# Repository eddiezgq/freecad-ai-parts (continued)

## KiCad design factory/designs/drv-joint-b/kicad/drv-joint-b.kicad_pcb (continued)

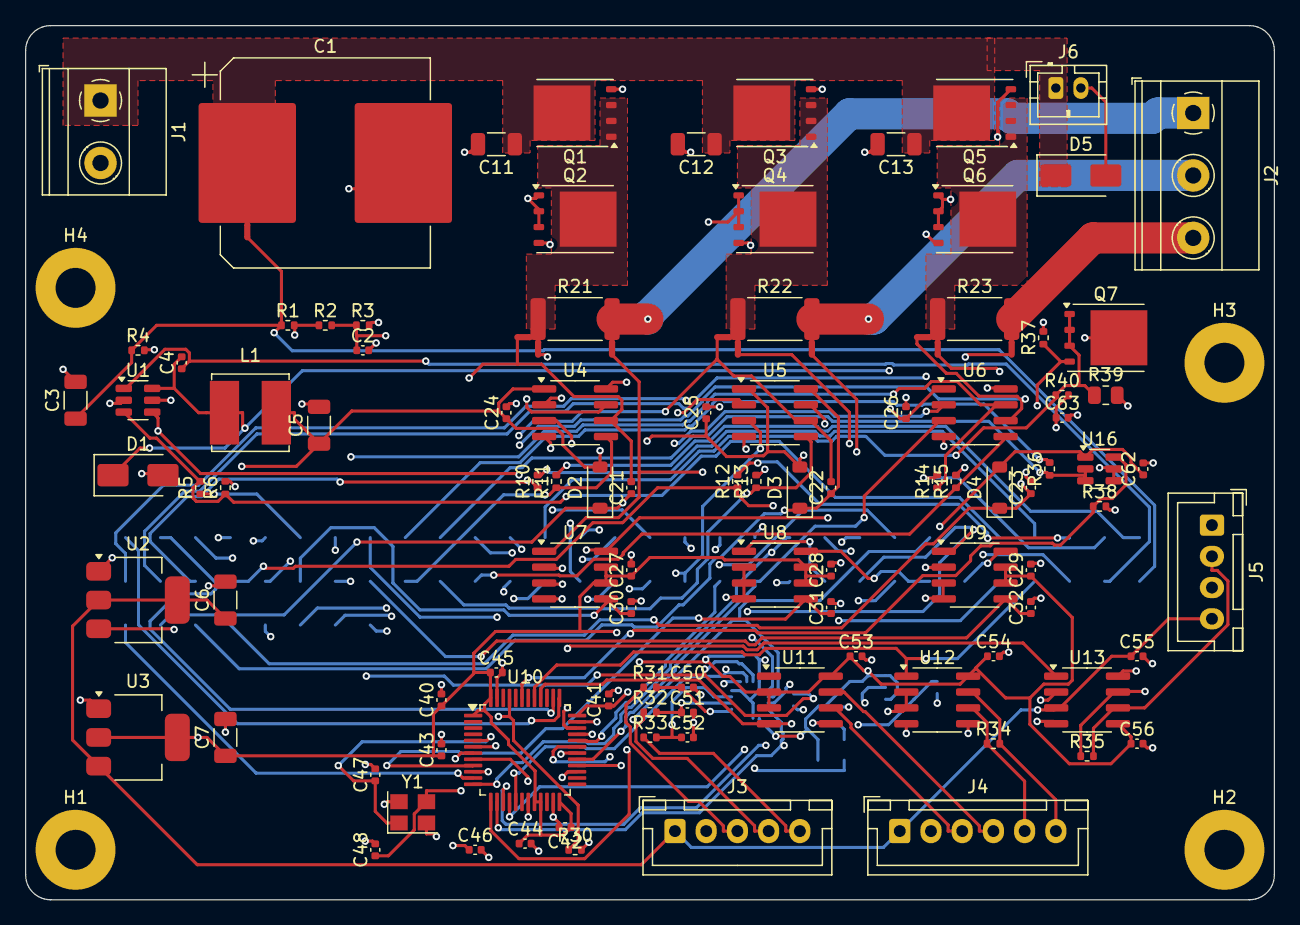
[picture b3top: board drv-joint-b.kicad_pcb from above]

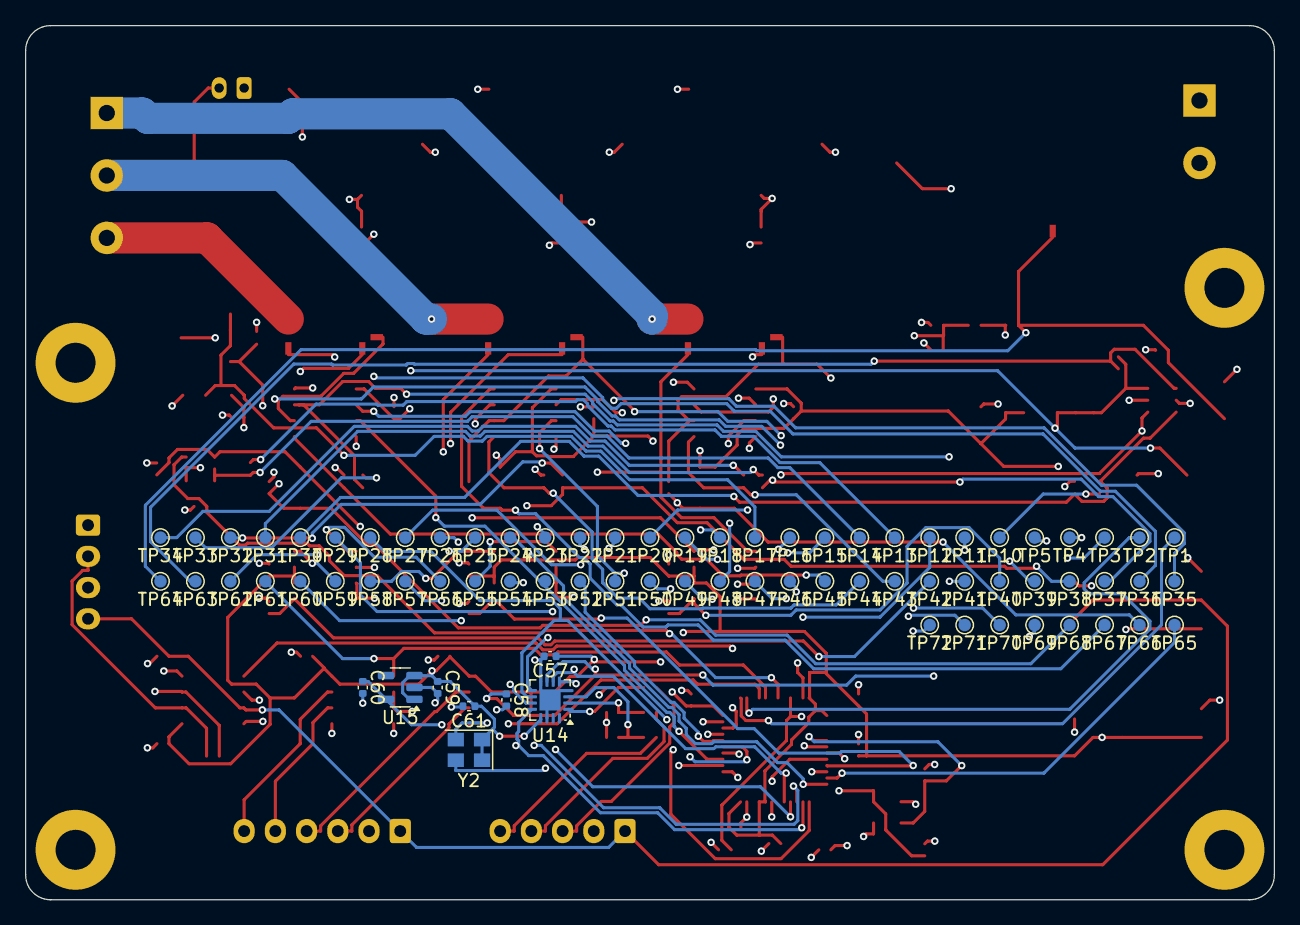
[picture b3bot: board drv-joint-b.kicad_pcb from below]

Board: 4 copper layers, 100.0 x 70.0 mm, 190 parts (76 on the bottom side), 86 nets.

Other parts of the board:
H1, H2, H3, H4: M3; MountingHole_3.2mm_M3_Pad

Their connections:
GND: H1.1, H2.1, H3.1, H4.1; also elsewhere on the board

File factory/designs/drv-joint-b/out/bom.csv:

物料编号,数值,封装,数量,位号,说明
CAP-0402,100n,C_0402_1005Metric,16,C4 C27 C28 C29 C40 C41 C42 C43 C46 C53 C54 C55 C56 C57 C58 C61,自举电容
CAP-0402,10n,C_0402_1005Metric,1,C2,
CAP-0402,10p,C_0402_1005Metric,2,C47 C48,
CAP-0402,1n,C_0402_1005Metric,3,C30 C31 C32,ADC 抗混叠
CAP-0402,1u,C_0402_1005Metric,5,C45 C59 C60 C62 C63,VDDA
CAP-0402,1u/25V,C_0402_1005Metric,6,C21 C22 C23 C24 C25 C26,自举电容
CAP-0402,220p,C_0402_1005Metric,3,C50 C51 C52,
CAP-0402,4.7u,C_0402_1005Metric,1,C44,
CAP-1206,10u/25V,C_1206_3216Metric,2,C6 C7,
CAP-1206,2.2u/100V,C_1206_3216Metric,4,C3 C11 C12 C13,
CAP-1206,22u/25V,C_1206_3216Metric,1,C5,
CAP-BULK,470u/63V,CP_Elec_16x17.5,1,C1,母线电容（例题 3）
CONN-PWR,48V IN,"TerminalBlock_Phoenix_MKDS-1,5-2_1x02_P5.00mm_Horizontal",1,J1,
CONN-PWR,MOTOR UVW,"TerminalBlock_Phoenix_MKDS-1,5-3_1x03_P5.00mm_Horizontal",1,J2,
CONN-SIG,BRAKE,JST_PH_B2B-PH-K_1x02_P2.00mm_Vertical,1,J6,抱闸线圈（失电制动，24 V 0.42 A，示例）：1 = 母线 +、2 = 线圈 −
CONN-SIG,CAN,JST_XH_B4B-XH-A_1x04_P2.50mm_Vertical,1,J5,
CONN-SIG,ENC ABZ,JST_XH_B5B-XH-A_1x05_P2.50mm_Vertical,1,J3,A/B/Z（2500 线，示例）
CONN-SIG,ENC SSI,JST_XH_B6B-XH-A_1x06_P2.50mm_Vertical,1,J4,输出端绝对值编码器
DIO-SMD,100V 1A,D_SOD-123,3,D2 D3 D4,自举二极管
DIO-SMD,60V 1A,D_SMA,1,D1,续流二极管
DIO-SMD-100,100V 1A,D_SMA,1,D5,抱闸线圈续流
IC-AMP,INA240A1D,SOIC-8_3.9x4.9mm_P1.27mm,3,U7 U8 U9,A 相电流采样放大 20 倍（示例选型）
IC-BUCK,LMR16006YQ,SOT-23-6,1,U1,48 V → 12 V 降压（示例选型）
IC-CAN,MCP2562-E/SN,SOIC-8_3.9x4.9mm_P1.27mm,1,U13,CAN 收发（示例选型）
IC-ENCIF,WQ-ENCIF,QFN-16-1EP_3x3mm_P0.5mm_EP1.7x1.7mm,1,U14,编码器接口芯片 WQ-ENCIF（第 92 轮设计，未流片）：滤波、4 倍频计数、SPI 从机
IC-GDRV,IR2101S,SOIC-8_3.9x4.9mm_P1.27mm,3,U4 U5 U6,A 相半桥驱动（示例选型）
IC-GDRV-LS,UCC27511ADBV,SOT-23-6,1,U16,抱闸栅极驱动（示例选型，第 110 轮）：12 V 供电，输入兼容 3.3 V
IC-LDO,AMS1117-3.3,SOT-223-3_TabPin2,1,U3,
IC-LDO,AMS1117-5.0,SOT-223-3_TabPin2,1,U2,
IC-LDO18,AP2112K-1.8,SOT-23-5,1,U15,芯片核心电源 1.8 V（示例选型）
IC-MCU-MC,STM32G431CBT6,LQFP-48_7x7mm_P0.5mm,1,U10,电机控制 MCU（示例选型）：TIM1 三相互补 PWM、ADC 采三相电流与母线、SPI1 读编码器接口芯片 U14、SPI3 读 SSI、TIM4_CH1（PB6）抱闸 PWM、FDCAN1
IC-RS485,MAX3485,SOIC-8_3.9x4.9mm_P1.27mm,2,U11 U12,SSI 时钟发送（示例选型）
IND-PWR,22u,L_Bourns_SRN6045TA,1,L1,
MOS-80V,BSC040N08NS5,TDSON-8-1,7,Q1 Q2 Q3 Q4 Q5 Q6 Q7,A 相上管（示例选型）
OSC-50M,50MHz,Oscillator_SMD_Abracon_ASE-4Pin_3.2x2.5mm,1,Y2,芯片时钟 50 MHz 有源晶振（示例选型）
RES-0402,10,R_0402_1005Metric,7,R10 R11 R12 R13 R14 R15 R36,栅极电阻（例题 2）
RES-0402,100k,R_0402_1005Metric,2,R4 R38,使能上拉
RES-0402,10k,R_0402_1005Metric,3,R6 R30 R37,反馈下电阻
RES-0402,120,R_0402_1005Metric,2,R34 R35,终端电阻
RES-0402,147k,R_0402_1005Metric,1,R5,反馈上电阻
RES-0402,1k,R_0402_1005Metric,4,R31 R32 R33 R40,编码器滤波（例题 4）
RES-0402,51k,R_0402_1005Metric,2,R1 R2,母线电压分压
RES-0402,6.8k,R_0402_1005Metric,1,R3,
RES-0805,0.5,R_0805_2012Metric,1,R39,抱闸线圈电流采样（第 114 轮）：0.5 Ω 在 Q7 源极，导通时电压 = 线圈电流 × 0.5 Ω（示例）
RES-SHUNT,2m 1%,R_2512_6332Metric,3,R21 R22 R23,A 相采样电阻（例题 1），两端开尔文引线到 INA240
XTAL,8MHz,Crystal_SMD_3225-4Pin_3.2x2.5mm,1,Y1,

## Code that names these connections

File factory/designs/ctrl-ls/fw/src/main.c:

/* 平缝机控制器 CTRL-LS 示例固件（第 159 轮 159f）。
 * 时间基准是 16 kHz 电流环中断（motor.c）；它每 1 ms 调一次缝纫状态机（sew.c 的 motor_ms_hook）。主循环只等中断。
 * 开机：量电流零点 → d 轴通电对零 → 低速转找编码器 Z 相（针杆最高点 = 主轴 0°）→ 停上针位 → 就绪。
 * 板上的调试口只有 SWD：遥测区 mc（电机）、sw（缝纫）、设置 cfg 给调试器看、改（仿真里由 Renode 读写内存）。
 * 没做的（留接口）：针距步进电机（TIM3 → PB4 / PB5）、操作面板串口（USART2 → PA2 / PA3）、联网、校正关断（PB9）。
 * 示例固件，仿真验证；电机未选型，参数见 README；不能直接用于产品。 */
#include <stdint.h>
#include "clock.h"
#include "motor.h"
#include "regs.h"
#include "sew.h"

int main(void)
{
    clock_init();
    sew_init();                 /* 电磁铁引脚先置成“不吸合” */
    motor_init();
    for (volatile uint32_t i = 0; i < 170000u; i++) {   /* 约 5 ms：电流零点（中断里量 64 个周期，4 ms） */
    }
    motor_start();
    for (;;) {
        __asm volatile("wfi");
    }
}
